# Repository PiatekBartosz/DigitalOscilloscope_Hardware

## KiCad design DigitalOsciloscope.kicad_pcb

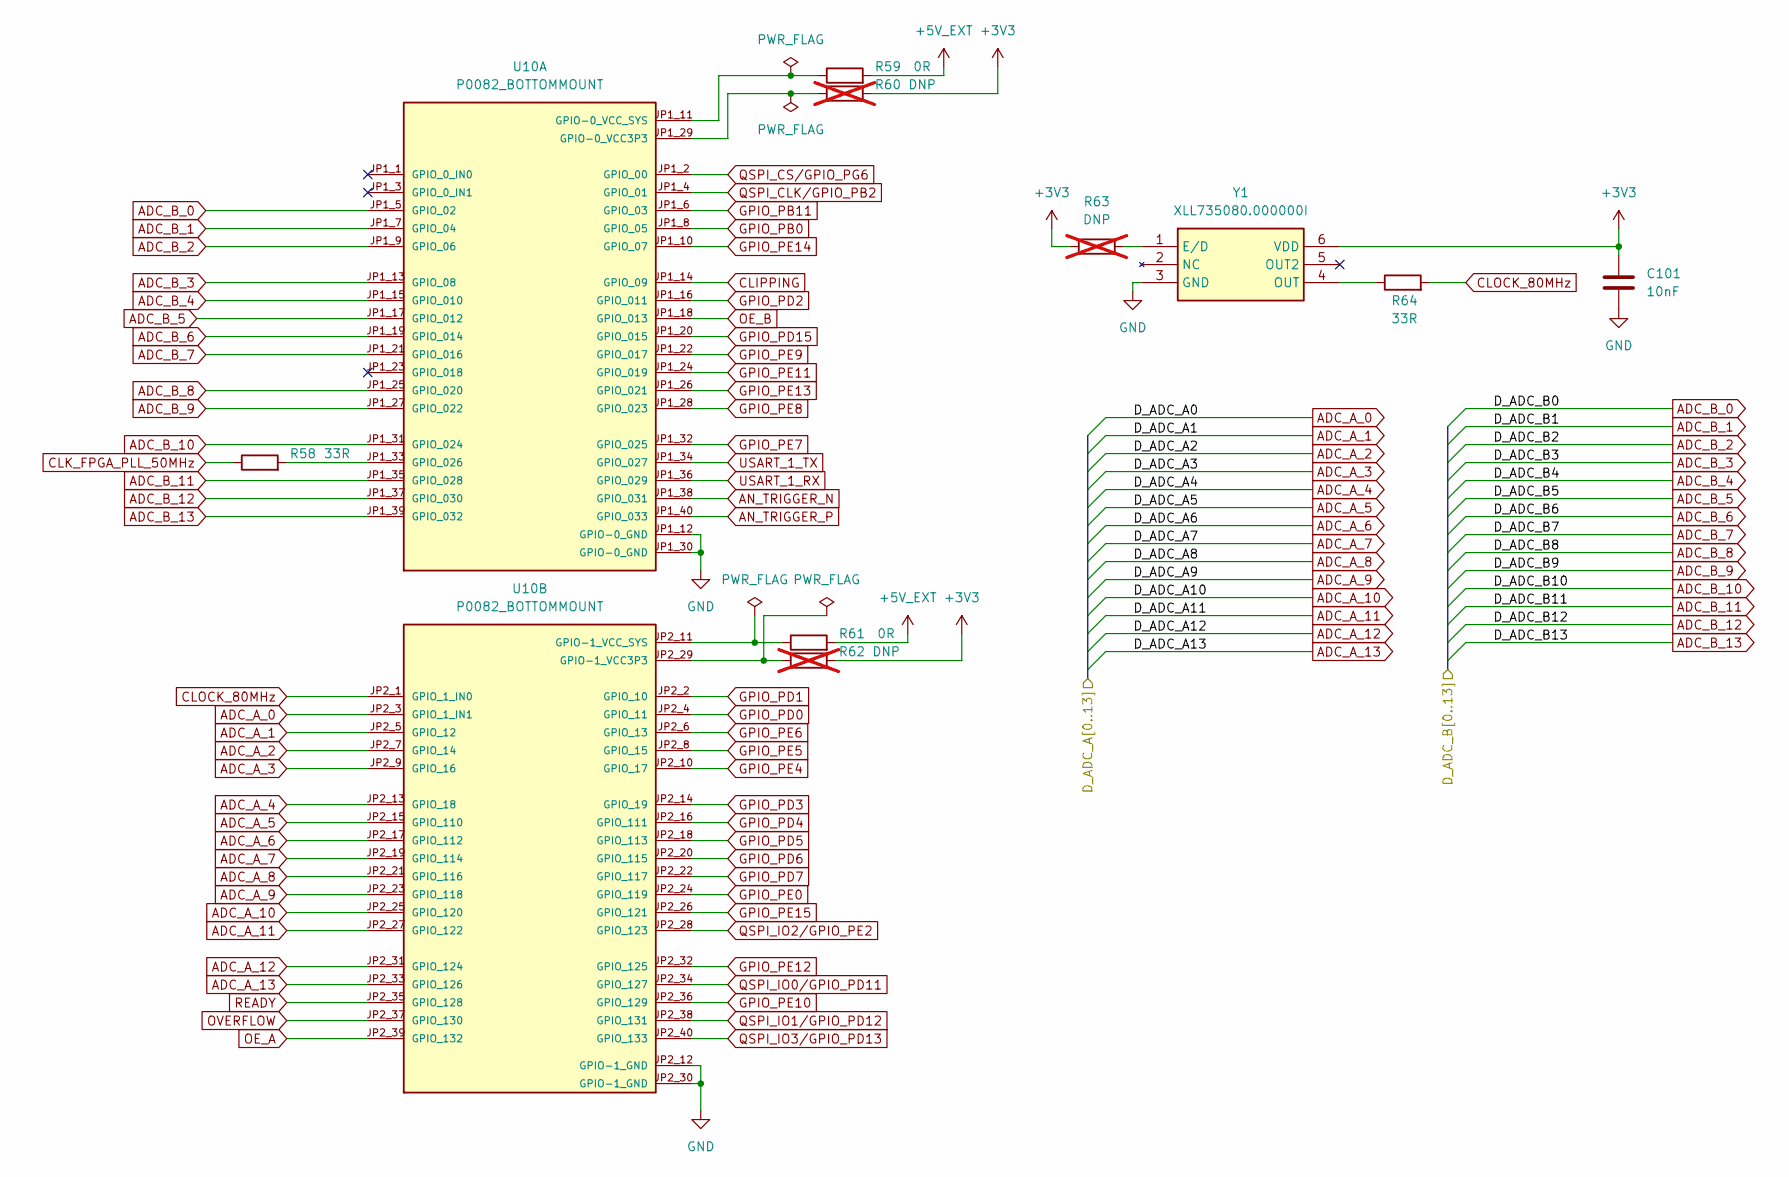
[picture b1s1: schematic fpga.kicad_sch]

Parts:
C101: 10nF; C_0805_2012Metric
R58, R64: 33R; R_0805_2012Metric
R59, R61: 0R; R_0805_2012Metric
R60, R62, R63: DNP; R_0805_2012Metric; not fitted
U10: P0082_BOTTOMMOUNT; MODULE_P0082_BOTTOMMOUNT; PARTREV V2.0
Y1: XLL735080.000000I; XLL735080000000I; Mouser Part Number 972-XLL735080000000I

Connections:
+3V3: C101.1, R60.2, R62.2, R63.1, Y1.6 (VDD); also elsewhere on the board
+5V_EXT: R59.2, R61.2; also elsewhere on the board
ADC_A_0: U10.JP2_3 (GPIO_1_IN1); also elsewhere on the board
ADC_A_1: U10.JP2_5 (GPIO_12); also elsewhere on the board
ADC_A_2: U10.JP2_7 (GPIO_14); also elsewhere on the board
ADC_A_3: U10.JP2_9 (GPIO_16); also elsewhere on the board
ADC_A_4: U10.JP2_13 (GPIO_18); also elsewhere on the board
ADC_A_5: U10.JP2_15 (GPIO_110); also elsewhere on the board
ADC_A_6: U10.JP2_17 (GPIO_112); also elsewhere on the board
ADC_A_7: U10.JP2_19 (GPIO_114); also elsewhere on the board
ADC_A_8: U10.JP2_21 (GPIO_116); also elsewhere on the board
ADC_A_9: U10.JP2_23 (GPIO_118); also elsewhere on the board
ADC_A_10: U10.JP2_25 (GPIO_120); also elsewhere on the board
ADC_A_11: U10.JP2_27 (GPIO_122); also elsewhere on the board
ADC_A_12: U10.JP2_31 (GPIO_124); also elsewhere on the board
ADC_A_13: U10.JP2_33 (GPIO_126); also elsewhere on the board
ADC_B_0: U10.JP1_5 (GPIO_02); also elsewhere on the board
ADC_B_1: U10.JP1_7 (GPIO_04); also elsewhere on the board
ADC_B_2: U10.JP1_9 (GPIO_06); also elsewhere on the board
ADC_B_3: U10.JP1_13 (GPIO_08); also elsewhere on the board
ADC_B_4: U10.JP1_15 (GPIO_010); also elsewhere on the board
ADC_B_5: U10.JP1_17 (GPIO_012); also elsewhere on the board
ADC_B_6: U10.JP1_19 (GPIO_014); also elsewhere on the board
ADC_B_7: U10.JP1_21 (GPIO_016); also elsewhere on the board
ADC_B_8: U10.JP1_25 (GPIO_020); also elsewhere on the board
ADC_B_9: U10.JP1_27 (GPIO_022); also elsewhere on the board
ADC_B_10: U10.JP1_31 (GPIO_024); also elsewhere on the board
ADC_B_11: U10.JP1_35 (GPIO_028); also elsewhere on the board
ADC_B_12: U10.JP1_37 (GPIO_030); also elsewhere on the board
ADC_B_13: U10.JP1_39 (GPIO_032); also elsewhere on the board
AN_TRIGGER_N: U10.JP1_38 (GPIO_031); also elsewhere on the board
AN_TRIGGER_P: U10.JP1_40 (GPIO_033); also elsewhere on the board
CLIPPING: U10.JP1_14 (GPIO_09); also elsewhere on the board
CLK_FPGA_PLL_50MHz: R58.1; also elsewhere on the board
CLOCK_80MHz: R64.2, U10.JP2_1 (GPIO_1_IN0); also elsewhere on the board
GND: C101.2, U10.JP1_12 (GPIO-0_GND), U10.JP1_30 (GPIO-0_GND), U10.JP2_12 (GPIO-1_GND), U10.JP2_30 (GPIO-1_GND), Y1.3 (GND); also elsewhere on the board
GPIO_PB0: U10.JP1_8 (GPIO_05); also elsewhere on the board
GPIO_PB11: U10.JP1_6 (GPIO_03); also elsewhere on the board
GPIO_PD0: U10.JP2_4 (GPIO_11); also elsewhere on the board
GPIO_PD1: U10.JP2_2 (GPIO_10); also elsewhere on the board
GPIO_PD2: U10.JP1_16 (GPIO_011); also elsewhere on the board
GPIO_PD3: U10.JP2_14 (GPIO_19); also elsewhere on the board
GPIO_PD4: U10.JP2_16 (GPIO_111); also elsewhere on the board
GPIO_PD5: U10.JP2_18 (GPIO_113); also elsewhere on the board
GPIO_PD6: U10.JP2_20 (GPIO_115); also elsewhere on the board
GPIO_PD7: U10.JP2_22 (GPIO_117); also elsewhere on the board
GPIO_PD15: U10.JP1_20 (GPIO_015); also elsewhere on the board
GPIO_PE0: U10.JP2_24 (GPIO_119); also elsewhere on the board
GPIO_PE4: U10.JP2_10 (GPIO_17); also elsewhere on the board
GPIO_PE5: U10.JP2_8 (GPIO_15); also elsewhere on the board
GPIO_PE6: U10.JP2_6 (GPIO_13); also elsewhere on the board
GPIO_PE7: U10.JP1_32 (GPIO_025); also elsewhere on the board
GPIO_PE8: U10.JP1_28 (GPIO_023); also elsewhere on the board
GPIO_PE9: U10.JP1_22 (GPIO_017); also elsewhere on the board
GPIO_PE10: U10.JP2_36 (GPIO_129); also elsewhere on the board
GPIO_PE11: U10.JP1_24 (GPIO_019); also elsewhere on the board
GPIO_PE12: U10.JP2_32 (GPIO_125); also elsewhere on the board
GPIO_PE13: U10.JP1_26 (GPIO_021); also elsewhere on the board
GPIO_PE14: U10.JP1_10 (GPIO_07); also elsewhere on the board
GPIO_PE15: U10.JP2_26 (GPIO_121); also elsewhere on the board
unnamed: R60.1, U10.JP1_29 (GPIO-0_VCC3P3)
unnamed: R59.1, U10.JP1_11 (GPIO-0_VCC_SYS)
unnamed: R58.2, U10.JP1_33 (GPIO_026)
unnamed: R62.1, U10.JP2_29 (GPIO-1_VCC3P3)
unnamed: R61.1, U10.JP2_11 (GPIO-1_VCC_SYS)
unnamed: R63.2, Y1.1 (E/D)
unnamed: R64.1, Y1.4 (OUT)
OE_A: U10.JP2_39 (GPIO_132); also elsewhere on the board
OE_B: U10.JP1_18 (GPIO_013); also elsewhere on the board
OVERFLOW: U10.JP2_37 (GPIO_130); also elsewhere on the board
QSPI_CLK/GPIO_PB2: U10.JP1_4 (GPIO_01); also elsewhere on the board
QSPI_CS/GPIO_PG6: U10.JP1_2 (GPIO_00); also elsewhere on the board
QSPI_IO0/GPIO_PD11: U10.JP2_34 (GPIO_127); also elsewhere on the board
QSPI_IO1/GPIO_PD12: U10.JP2_38 (GPIO_131); also elsewhere on the board
QSPI_IO2/GPIO_PE2: U10.JP2_28 (GPIO_123); also elsewhere on the board
QSPI_IO3/GPIO_PD13: U10.JP2_40 (GPIO_133); also elsewhere on the board
READY: U10.JP2_35 (GPIO_128); also elsewhere on the board
USART_1_RX: U10.JP1_36 (GPIO_029); also elsewhere on the board
USART_1_TX: U10.JP1_34 (GPIO_027); also elsewhere on the board

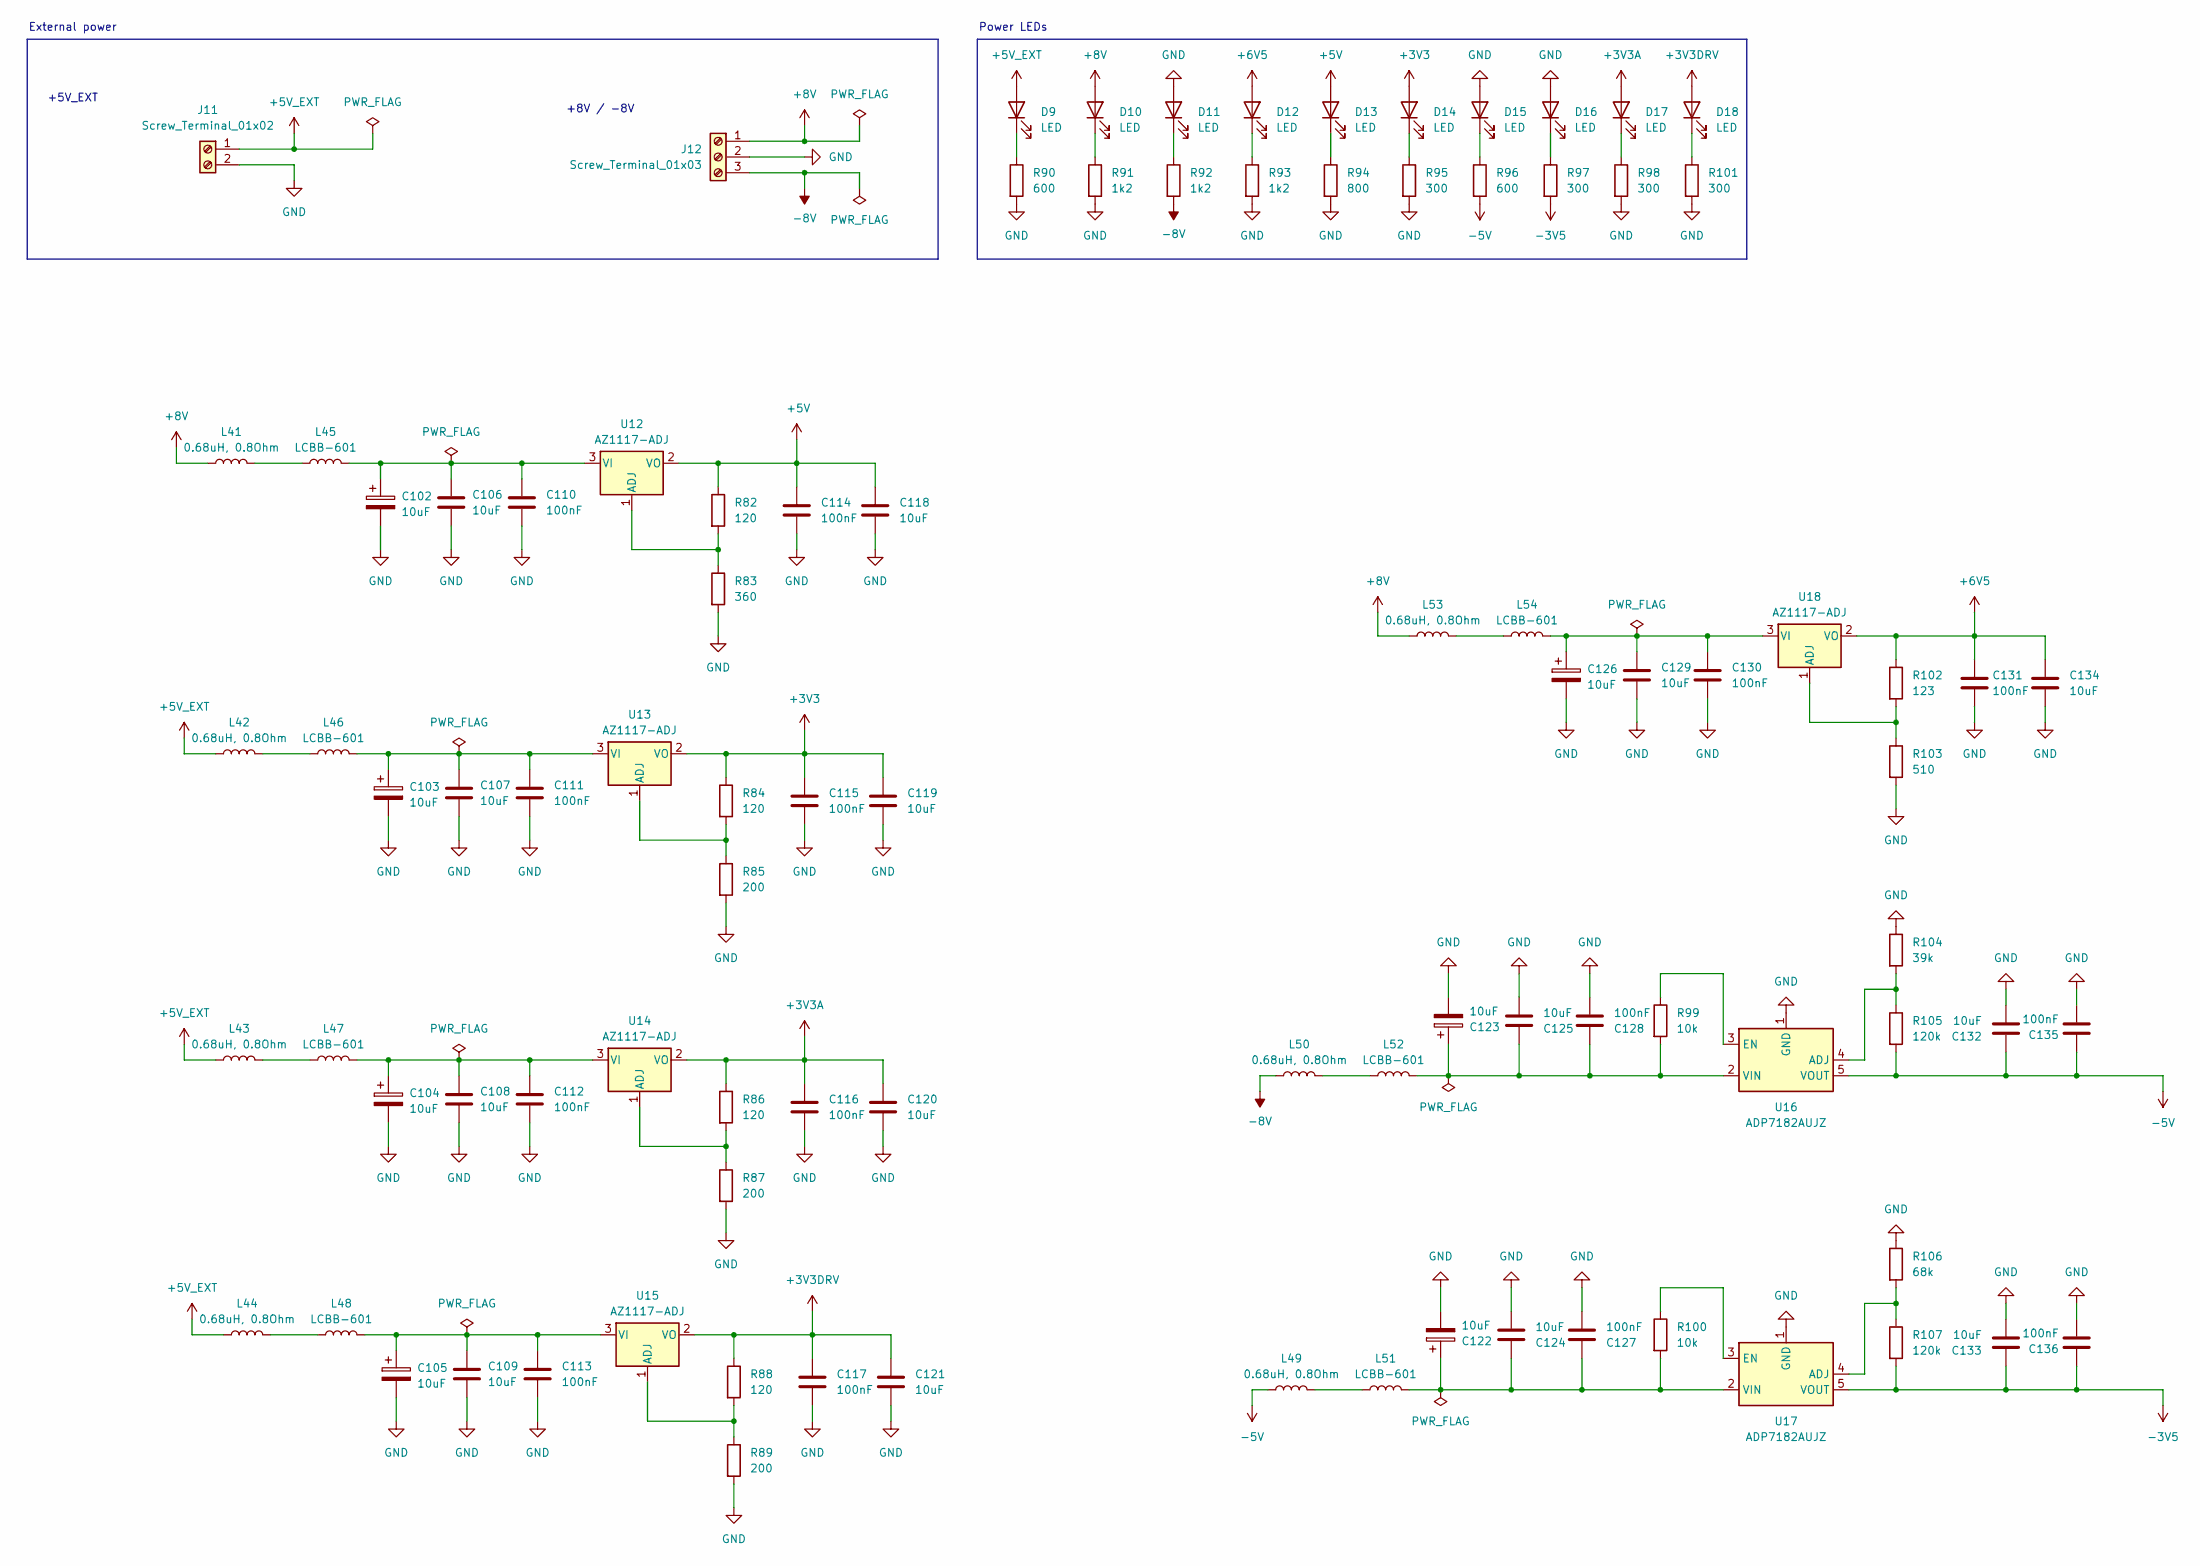
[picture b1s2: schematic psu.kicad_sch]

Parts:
C102, C103, C104, C105, C122, C123, C126: 10uF; CP_Elec_5x4.4
C106, C107, C108, C109, C118, C119, C120, C121, C124, C125, C129, C132, C133, C134: 10uF; C_0805_2012Metric
C110, C111, C112, C113, C114, C115, C116, C117, C127, C128, C130, C131, C135, C136: 100nF; C_0805_2012Metric
D9, D10, D11, D12, D13, D14, D15, D16, D17, D18: LED; LED_0805_2012Metric
J11: Screw_Terminal_01x02; TerminalBlock_MaiXu_MX126-5.0-02P_1x02_P5.00mm
J12: Screw_Terminal_01x03; TerminalBlock_MaiXu_MX126-5.0-03P_1x03_P5.00mm
L41, L42, L43, L44, L49, L50, L53: 0.68uH, 0.8Ohm; L_0805_2012Metric
L45, L46, L47, L48, L51, L52, L54: LCBB-601; L_0805_2012Metric
R82, R84, R86, R88: 120; R_0805_2012Metric
R83: 360; R_0805_2012Metric
R85, R87, R89: 200; R_0805_2012Metric
R90, R96: 600; R_0805_2012Metric
R91, R92, R93: 1k2; R_0805_2012Metric
R94: 800; R_0805_2012Metric
R95, R97, R98, R101: 300; R_0805_2012Metric
R99, R100: 10k; R_0805_2012Metric
R102: 123; R_0805_2012Metric
R103: 510; R_0805_2012Metric
R104: 39k; R_0805_2012Metric
R105, R107: 120k; R_0805_2012Metric
R106: 68k; R_0805_2012Metric
U12, U13, U14, U15, U18: AZ1117-ADJ; SOT-89-3
U16, U17: ADP7182AUJZ; TSOT-23-5

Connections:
+3V3: C115.1, C119.1, D14.2 (A), R84.1, U13.2 (VO); also elsewhere on the board
+3V3A: C116.1, C120.1, D17.2 (A), R86.1, U14.2 (VO); also elsewhere on the board
+3V3DRV: C117.1, C121.1, D18.2 (A), R88.1, U15.2 (VO); also elsewhere on the board
+5V: C114.1, C118.1, D13.2 (A), R82.1, U12.2 (VO); also elsewhere on the board
+5V_EXT: D9.2 (A), J11.1, L42.1, L43.1, L44.1; also elsewhere on the board
+6V5: C131.1, C134.1, D12.2 (A), R102.1, U18.2 (VO); also elsewhere on the board
+8V: D10.2 (A), J12.1, L41.1, L53.1; also elsewhere on the board
-3V5: C133.1, C136.1, R97.2, R107.2, U17.5 (VOUT); also elsewhere on the board
-5V: C132.1, C135.1, L49.1, R96.2, R105.2, U16.5 (VOUT); also elsewhere on the board
-8V: J12.3, L50.1, R92.2
GND: C102.2, C103.2, C104.2, C105.2, C106.2, C107.2, C108.2, C109.2, C110.2, C111.2, C112.2, C113.2, C114.2, C115.2, C116.2, C117.2, C118.2, C119.2, C120.2, C121.2, C122.2, C123.2, C124.2, C125.2, C126.2, C127.2, C128.2, C129.2, C130.2, C131.2, C132.2, C133.2, C134.2, C135.2, C136.2, D11.2 (A), D15.2 (A), D16.2 (A), J11.2, J12.2, R83.2, R85.2, R87.2, R89.2, R90.2, R91.2, R93.2, R94.2, R95.2, R98.2, R101.2, R103.2, R104.1, R106.1, U16.1 (GND), U17.1 (GND); also elsewhere on the board
unnamed: D9.1 (K), R90.1
unnamed: D10.1 (K), R91.1
unnamed: D11.1 (K), R92.1
unnamed: D12.1 (K), R93.1
unnamed: D13.1 (K), R94.1
unnamed: D14.1 (K), R95.1
unnamed: D15.1 (K), R96.1
unnamed: D16.1 (K), R97.1
unnamed: D17.1 (K), R98.1
unnamed: D18.1 (K), R101.1
unnamed: L41.2, L45.1
unnamed: L42.2, L46.1
unnamed: L43.2, L47.1
unnamed: L44.2, L48.1
unnamed: L49.2, L51.1
unnamed: L50.2, L52.1
unnamed: L53.2, L54.1
unnamed: R82.2, R83.1, U12.1 (ADJ)
unnamed: C102.1, C106.1, C110.1, L45.2, U12.3 (VI)
unnamed: R84.2, R85.1, U13.1 (ADJ)
unnamed: C103.1, C107.1, C111.1, L46.2, U13.3 (VI)
unnamed: R86.2, R87.1, U14.1 (ADJ)
unnamed: C104.1, C108.1, C112.1, L47.2, U14.3 (VI)
unnamed: R88.2, R89.1, U15.1 (ADJ)
unnamed: C105.1, C109.1, C113.1, L48.2, U15.3 (VI)
unnamed: R104.2, R105.1, U16.4 (ADJ)
unnamed: R99.1, U16.3 (EN)
unnamed: C123.1, C125.1, C128.1, L52.2, R99.2, U16.2 (VIN)
unnamed: R106.2, R107.1, U17.4 (ADJ)
unnamed: R100.1, U17.3 (EN)
unnamed: C122.1, C124.1, C127.1, L51.2, R100.2, U17.2 (VIN)
unnamed: R102.2, R103.1, U18.1 (ADJ)
unnamed: C126.1, C129.1, C130.1, L54.2, U18.3 (VI)

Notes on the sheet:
+8V / -8V
External power
Power LEDs
+5V_EXT

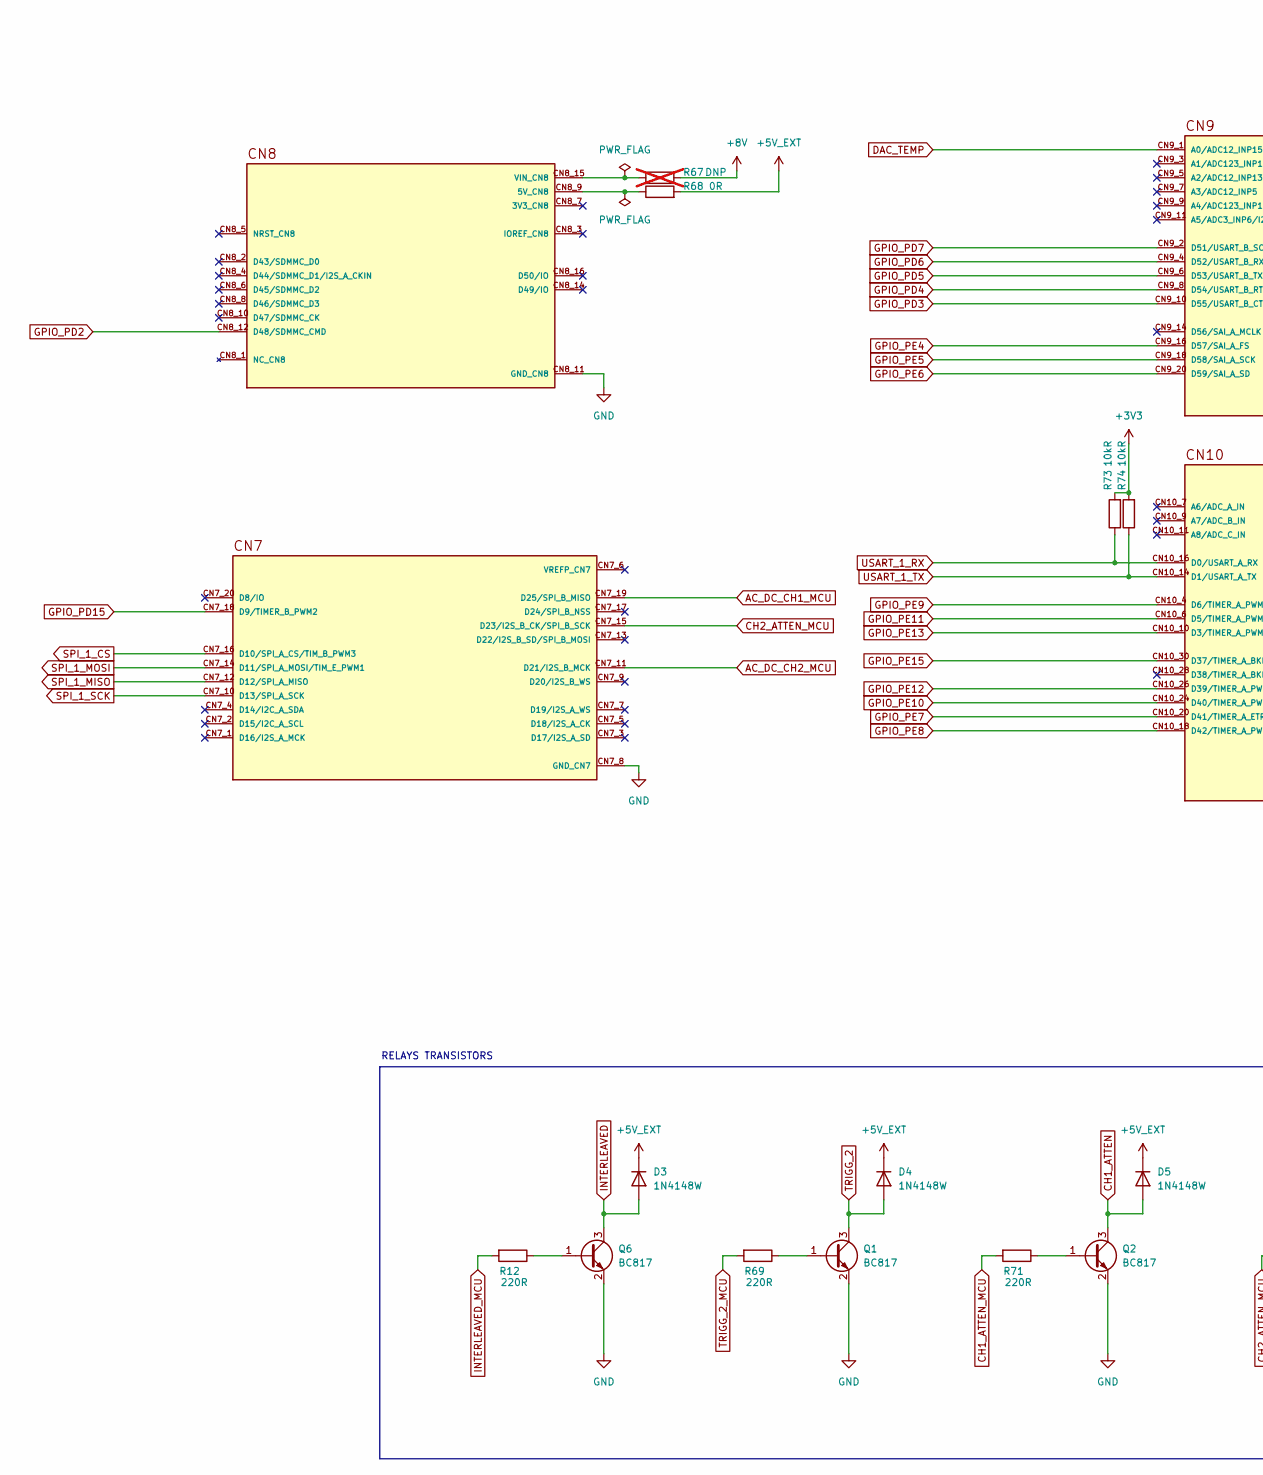
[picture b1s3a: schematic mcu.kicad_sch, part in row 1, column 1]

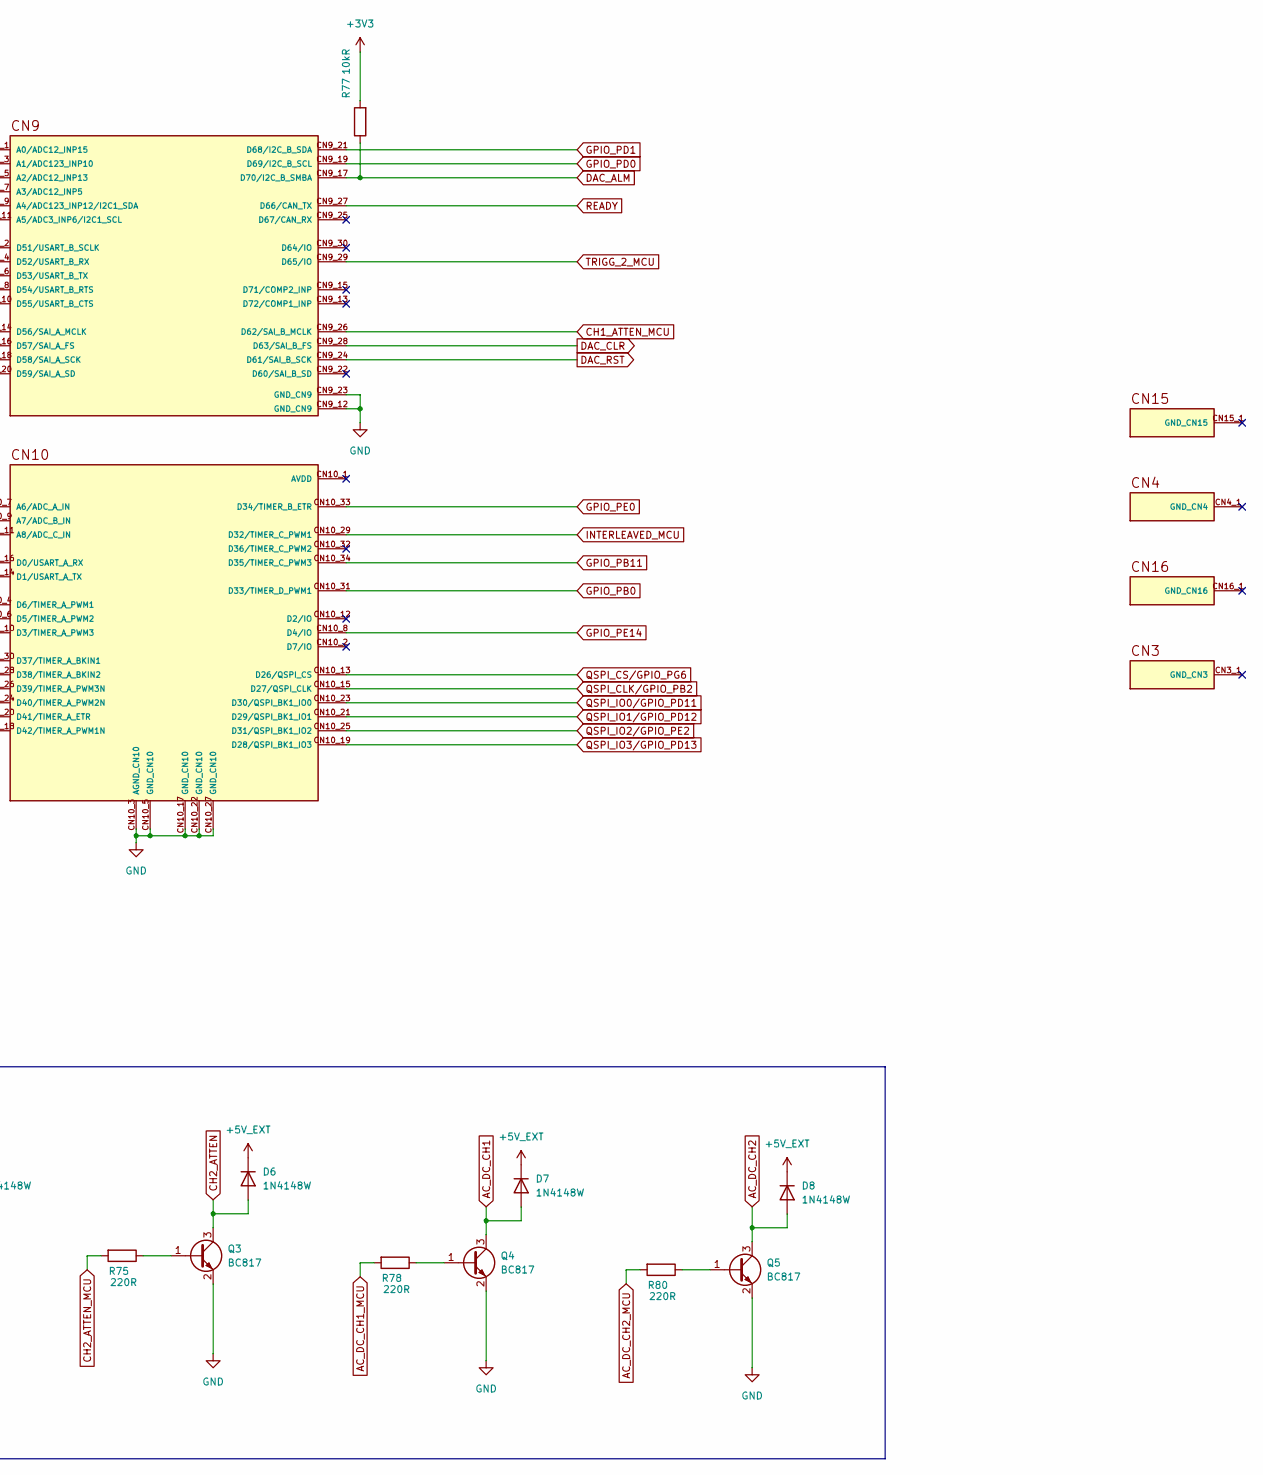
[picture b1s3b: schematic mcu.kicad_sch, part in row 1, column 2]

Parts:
D3, D4, D5, D6, D7, D8: 1N4148W; D_SOD-123
Q1, Q2, Q3, Q4, Q5, Q6: BC817; SOT-23
R12, R69, R71, R75, R78, R80: 220R; R_0805_2012Metric
R67: DNP; R_0805_2012Metric; not fitted
R68: 0R; R_0805_2012Metric
R73, R74, R77: 10kR; R_0805_2012Metric
U11: NUCLEOH723ZG; MODULE_NUCLEOH723ZG; PARTREV 2

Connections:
+3V3: R73.2, R74.2, R77.2; also elsewhere on the board
+5V_EXT: D3.1 (K), D4.1 (K), D5.1 (K), D6.1 (K), D7.1 (K), D8.1 (K), R68.2; also elsewhere on the board
+8V: R67.2; also elsewhere on the board
AC_DC_CH1: D7.2 (A), Q4.3 (C); also elsewhere on the board
AC_DC_CH1_MCU: R78.2, U11.CN7_19 (D25/SPI_B_MISO)
AC_DC_CH2: D8.2 (A), Q5.3 (C); also elsewhere on the board
AC_DC_CH2_MCU: R80.2, U11.CN7_11 (D21/I2S_B_MCK)
CH1_ATTEN: D5.2 (A), Q2.3 (C); also elsewhere on the board
CH1_ATTEN_MCU: R71.2, U11.CN9_26 (D62/SAI_B_MCLK)
CH2_ATTEN: D6.2 (A), Q3.3 (C); also elsewhere on the board
CH2_ATTEN_MCU: R75.2, U11.CN7_15 (D23/I2S_B_CK/SPI_B_SCK)
DAC_ALM: R77.1, U11.CN9_17 (D70/I2C_B_SMBA); also elsewhere on the board
DAC_CLR: U11.CN9_28 (D63/SAI_B_FS); also elsewhere on the board
DAC_RST: U11.CN9_24 (D61/SAI_B_SCK); also elsewhere on the board
DAC_TEMP: U11.CN9_1 (A0/ADC12_INP15); also elsewhere on the board
GND: Q1.2 (E), Q2.2 (E), Q3.2 (E), Q4.2 (E), Q5.2 (E), Q6.2 (E), U11.CN7_8 (GND_CN7), U11.CN8_11 (GND_CN8), U11.CN8_13 (GND_CN8), U11.CN9_12 (GND_CN9), U11.CN9_23 (GND_CN9), U11.CN10_3 (AGND_CN10), U11.CN10_5 (GND_CN10), U11.CN10_17 (GND_CN10), U11.CN10_22 (GND_CN10), U11.CN10_27 (GND_CN10); also elsewhere on the board
GPIO_PB0: U11.CN10_31 (D33/TIMER_D_PWM1); also elsewhere on the board
GPIO_PB11: U11.CN10_34 (D35/TIMER_C_PWM3); also elsewhere on the board
GPIO_PD0: U11.CN9_19 (D69/I2C_B_SCL); also elsewhere on the board
GPIO_PD1: U11.CN9_21 (D68/I2C_B_SDA); also elsewhere on the board
GPIO_PD2: U11.CN8_12 (D48/SDMMC_CMD); also elsewhere on the board
GPIO_PD3: U11.CN9_10 (D55/USART_B_CTS); also elsewhere on the board
GPIO_PD4: U11.CN9_8 (D54/USART_B_RTS); also elsewhere on the board
GPIO_PD5: U11.CN9_6 (D53/USART_B_TX); also elsewhere on the board
GPIO_PD6: U11.CN9_4 (D52/USART_B_RX); also elsewhere on the board
GPIO_PD7: U11.CN9_2 (D51/USART_B_SCLK); also elsewhere on the board
GPIO_PD15: U11.CN7_18 (D9/TIMER_B_PWM2); also elsewhere on the board
GPIO_PE0: U11.CN10_33 (D34/TIMER_B_ETR); also elsewhere on the board
GPIO_PE4: U11.CN9_16 (D57/SAI_A_FS); also elsewhere on the board
GPIO_PE5: U11.CN9_18 (D58/SAI_A_SCK); also elsewhere on the board
GPIO_PE6: U11.CN9_20 (D59/SAI_A_SD); also elsewhere on the board
GPIO_PE7: U11.CN10_20 (D41/TIMER_A_ETR); also elsewhere on the board
GPIO_PE8: U11.CN10_18 (D42/TIMER_A_PWM1N); also elsewhere on the board
GPIO_PE9: U11.CN10_4 (D6/TIMER_A_PWM1); also elsewhere on the board
GPIO_PE10: U11.CN10_24 (D40/TIMER_A_PWM2N); also elsewhere on the board
GPIO_PE11: U11.CN10_6 (D5/TIMER_A_PWM2); also elsewhere on the board
GPIO_PE12: U11.CN10_26 (D39/TIMER_A_PWM3N); also elsewhere on the board
GPIO_PE13: U11.CN10_10 (D3/TIMER_A_PWM3); also elsewhere on the board
GPIO_PE14: U11.CN10_8 (D4/IO); also elsewhere on the board
GPIO_PE15: U11.CN10_30 (D37/TIMER_A_BKIN1); also elsewhere on the board
INTERLEAVED: D3.2 (A), Q6.3 (C); also elsewhere on the board
INTERLEAVED_MCU: R12.2, U11.CN10_29 (D32/TIMER_C_PWM1)
unnamed: Q1.1 (B), R69.1
unnamed: Q2.1 (B), R71.1
unnamed: Q3.1 (B), R75.1
unnamed: Q4.1 (B), R78.1
unnamed: Q5.1 (B), R80.1
unnamed: Q6.1 (B), R12.1
unnamed: R68.1, U11.CN8_9 (5V_CN8)
unnamed: R67.1, U11.CN8_15 (VIN_CN8)
QSPI_CLK/GPIO_PB2: U11.CN10_15 (D27/QSPI_CLK); also elsewhere on the board
QSPI_CS/GPIO_PG6: U11.CN10_13 (D26/QSPI_CS); also elsewhere on the board
QSPI_IO0/GPIO_PD11: U11.CN10_23 (D30/QSPI_BK1_IO0); also elsewhere on the board
QSPI_IO1/GPIO_PD12: U11.CN10_21 (D29/QSPI_BK1_IO1); also elsewhere on the board
QSPI_IO2/GPIO_PE2: U11.CN10_25 (D31/QSPI_BK1_IO2); also elsewhere on the board
QSPI_IO3/GPIO_PD13: U11.CN10_19 (D28/QSPI_BK1_IO3); also elsewhere on the board
READY: U11.CN9_27 (D66/CAN_TX); also elsewhere on the board
SPI_1_CS: U11.CN7_16 (D10/SPI_A_CS/TIM_B_PWM3); also elsewhere on the board
SPI_1_MISO: U11.CN7_12 (D12/SPI_A_MISO); also elsewhere on the board
SPI_1_MOSI: U11.CN7_14 (D11/SPI_A_MOSI/TIM_E_PWM1); also elsewhere on the board
SPI_1_SCK: U11.CN7_10 (D13/SPI_A_SCK); also elsewhere on the board
TRIGG_2: D4.2 (A), Q1.3 (C); also elsewhere on the board
TRIGG_2_MCU: R69.2, U11.CN9_29 (D65/IO)
USART_1_RX: R73.1, U11.CN10_16 (D0/USART_A_RX); also elsewhere on the board
USART_1_TX: R74.1, U11.CN10_14 (D1/USART_A_TX); also elsewhere on the board

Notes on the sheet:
RELAYS TRANSISTORS

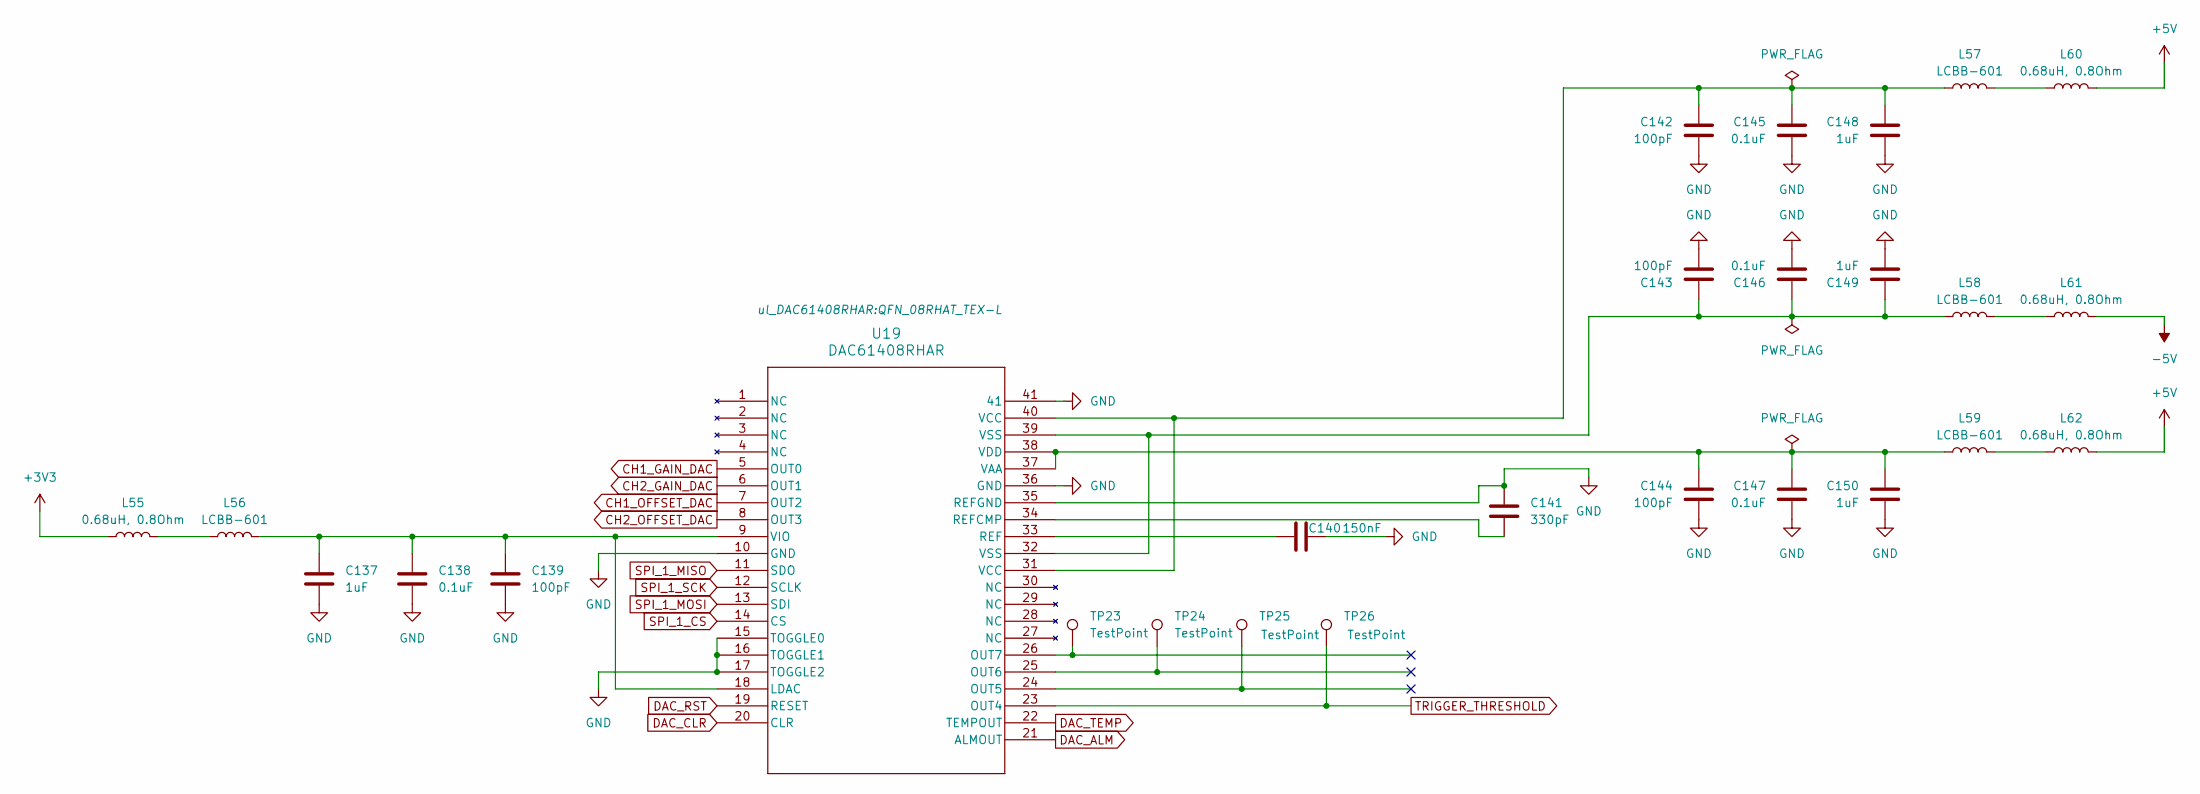
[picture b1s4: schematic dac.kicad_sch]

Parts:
C137, C148, C149, C150: 1uF; C_0805_2012Metric
C138, C145, C146, C147: 0.1uF; C_0805_2012Metric
C139, C142, C143, C144: 100pF; C_0805_2012Metric
C140: 150nF; C_0805_2012Metric
C141: 330pF; C_0805_2012Metric
L55, L60, L61, L62: 0.68uH, 0.8Ohm; L_0805_2012Metric
L56, L57, L58, L59: LCBB-601; L_0805_2012Metric
TP23, TP24, TP25, TP26: TestPoint; TestPoint_Pad_D1.0mm
U19: DAC61408RHAR; QFN_08RHAT_TEX-L

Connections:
+3V3: L55.1; also elsewhere on the board
+5V: L60.1, L62.1; also elsewhere on the board
-5V: L61.1; also elsewhere on the board
CH1_GAIN_DAC: U19.5 (OUT0); also elsewhere on the board
CH1_OFFSET_DAC: U19.7 (OUT2); also elsewhere on the board
CH2_GAIN_DAC: U19.6 (OUT1); also elsewhere on the board
CH2_OFFSET_DAC: U19.8 (OUT3); also elsewhere on the board
DAC_ALM: U19.21 (ALMOUT); also elsewhere on the board
DAC_CLR: U19.20 (CLR); also elsewhere on the board
DAC_RST: U19.19 (RESET); also elsewhere on the board
DAC_TEMP: U19.22 (TEMPOUT); also elsewhere on the board
GND: C137.2, C138.2, C139.2, C140.2, C141.1, C142.2, C143.2, C144.2, C145.2, C146.2, C147.2, C148.2, C149.2, C150.2, U19.10 (GND), U19.15 (TOGGLE0), U19.16 (TOGGLE1), U19.17 (TOGGLE2), U19.35 (REFGND), U19.36 (GND), U19.41; also elsewhere on the board
unnamed: C142.1, C145.1, C148.1, L57.2, U19.31 (VCC), U19.40 (VCC)
unnamed: C143.1, C146.1, C149.1, L58.2, U19.32 (VSS), U19.39 (VSS)
unnamed: L55.2, L56.1
unnamed: L57.1, L60.2
unnamed: L58.1, L61.2
unnamed: L59.1, L62.2
unnamed: C137.1, C138.1, C139.1, L56.2, U19.9 (VIO), U19.18 (LDAC)
unnamed: C140.1, U19.33 (REF)
unnamed: C141.2, U19.34 (REFCMP)
unnamed: C144.1, C147.1, C150.1, L59.2, U19.37 (VAA), U19.38 (VDD)
SPI_1_CS: U19.14 (CS); also elsewhere on the board
SPI_1_MISO: U19.11 (SDO); also elsewhere on the board
SPI_1_MOSI: U19.13 (SDI); also elsewhere on the board
SPI_1_SCK: U19.12 (SCLK); also elsewhere on the board
TRIGGER_THRESHOLD: TP26.1, U19.23 (OUT4); also elsewhere on the board
